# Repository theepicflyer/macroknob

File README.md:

# macroknob

A simple 2-key, 1 rotary encoder shield for ZMK. Designed to complement any ZMK keyboard as a dongle.

This repo contains the PCB and case files for the MacroKnob. The software (shield config) can be found here: https://github.com/theepicflyer/macroknob-shield.

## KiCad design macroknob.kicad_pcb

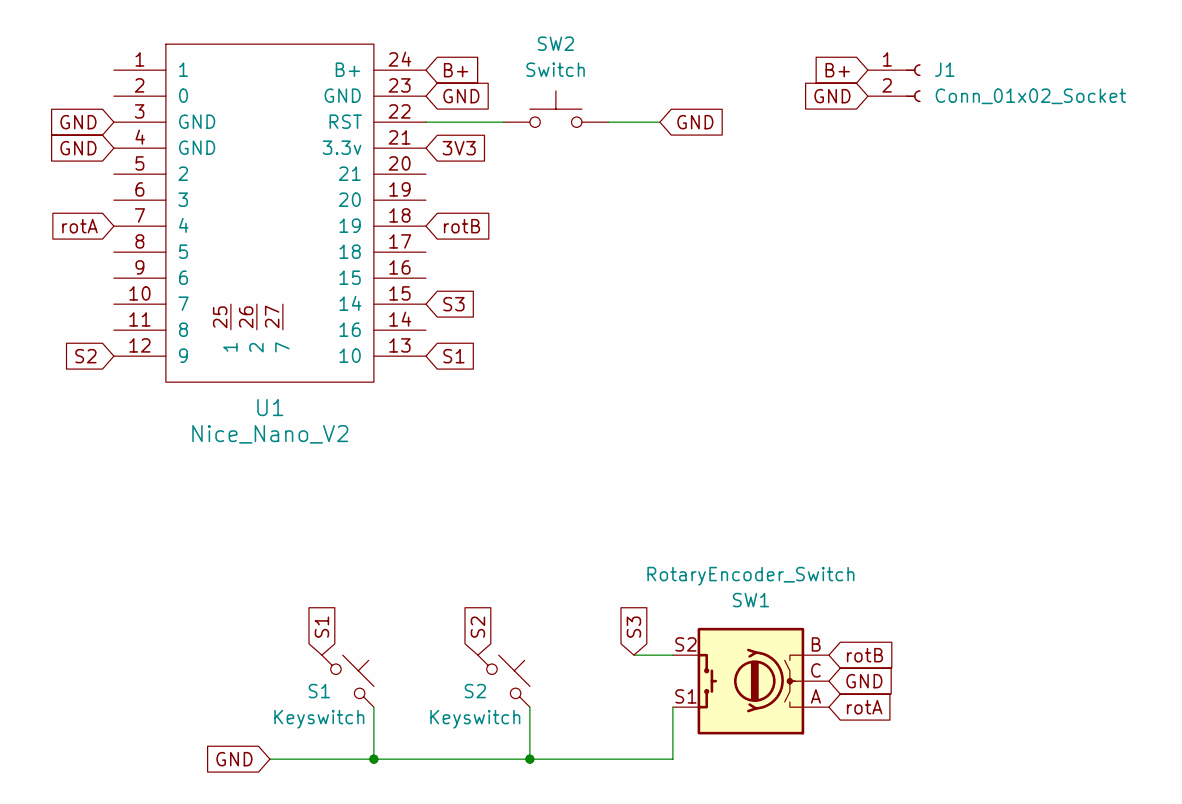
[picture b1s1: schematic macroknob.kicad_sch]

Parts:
J1: Conn_01x02_Socket; JST_PH_S2B-PH-K_1x02_P2.00mm_Horizontal
S1, S2: Keyswitch; MX_PCB_1.00u
SW1: RotaryEncoder_Switch; Encoder_EC11_MX
SW2: Switch; SW_SPST_PTS810
U1: Nice_Nano_V2

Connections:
3V3: U1.21 (3.3v)
B+: J1.1, U1.24 (B+)
GND: J1.2, S1.2, S2.2, SW1.C, SW1.S1, SW2.2, U1.3 (GND), U1.4 (GND), U1.23 (GND)
unnamed: SW2.1, U1.22 (RST)
S1: S1.1, U1.13 (10)
S2: S2.1, U1.12 (9)
S3: SW1.S2, U1.15 (14)
rotA: SW1.A, U1.7 (4)
rotB: SW1.B, U1.18 (19)

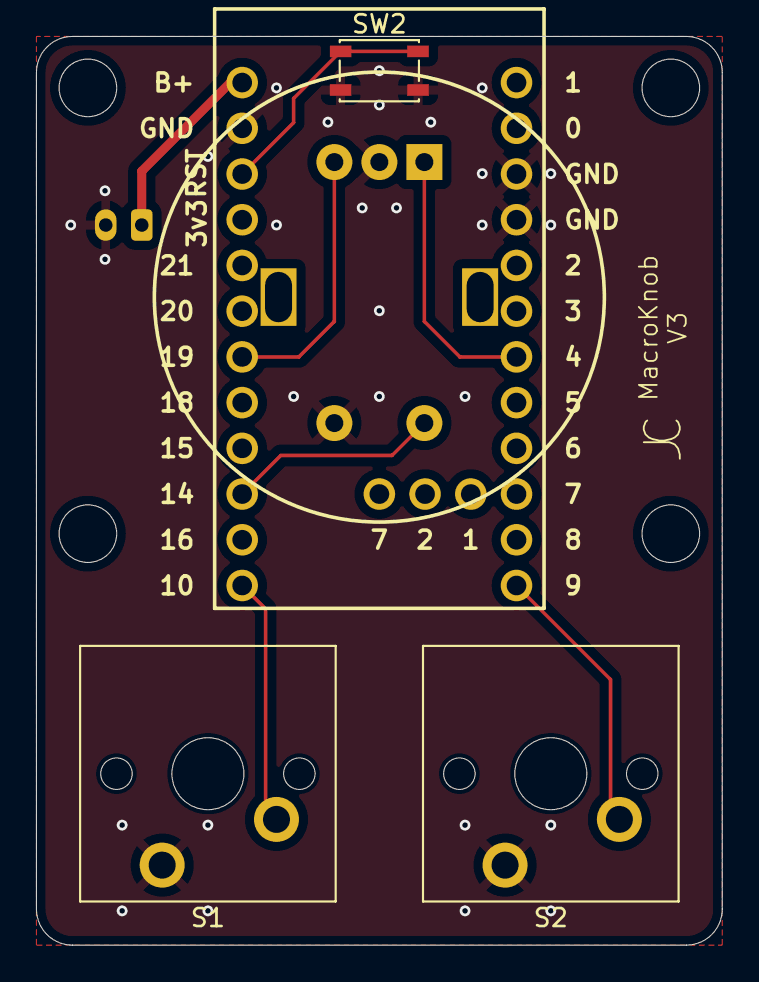
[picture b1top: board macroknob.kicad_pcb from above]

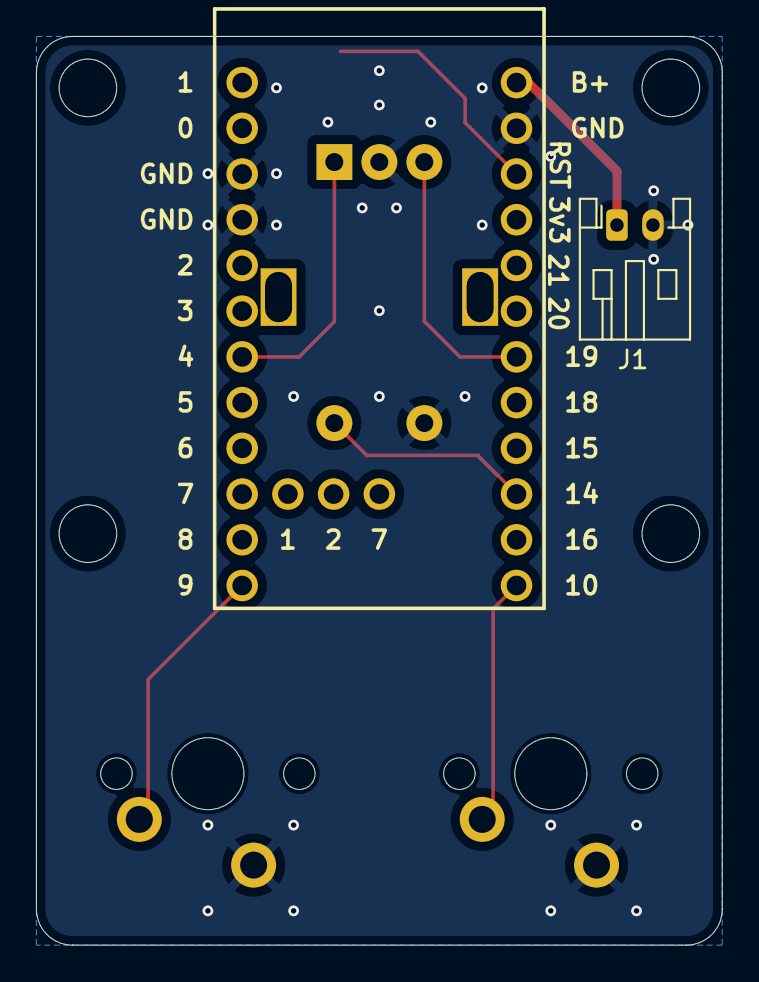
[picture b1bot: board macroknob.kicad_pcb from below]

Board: 2 copper layers, 38.1 x 50.5 mm, 6 parts (2 on the bottom side), 8 nets.

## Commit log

2024-12-29 Initial - V1
2025-01-12 Add schematic pdf
2025-01-12 Add V3 and case stl
2026-02-10 Update README with image and improved description
    Added an image and updated the description for clarity.
